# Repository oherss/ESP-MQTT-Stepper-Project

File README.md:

# ESP MQTT Stepper Project

This project is an integration between the TMC 2209 stepper driver with an ESP 32-S3 chip and code that allows the motor to connect via MQTT with a custom protocol.
The code parts of this project are made to be compatible with the PD Stepper hardware project.
The hardware is also inspired by this project, but without some of the extra bells and whistles, like PD power, expansion ports and buttons.

# This is a student project
Which means I am doing this for an exam and may not maintain this repo in the future, this is mostly a proof-of-concept.
This also means the directories may be kind of confusing, and there is also some extra code in here for an unrelated project, so don't mind my mess :)

# Hardware
The hardware, just like the PD-Stepper project is meant to be attached to the back of an ordinary Nema 17 stepper motor.
# PCB
As mentioned, this is based on the PD-Stepper project, but with just the essentials, mostly to make it cheaper to produce.
This means we still get the TMC 2209 silent stepper motor driver, and the flexible ESP-32-s3 microprocessor, but I have done away with the I2C and AUX port, USB-C Power Delivery and I have also replaced the unobtainum power-regulator (MPM-3612-33) and replaced it with a commonplace alternative.
In the PCB folder I have both the fabrication files, complete with BOM and assemply files, so you don't need to solder the components yourself.
The files have been prepared for them to be produced via JLC-PCB, so if you want to use another fabricator, the files may not work.
There is also the project files for KiCAD 7.0 files to work on the schematic if you'd like, although I have a few components with custom libraries, which might make it annoying to initially set up.
# Other Hardware
In the future I'd like to get some 3D-models for 3D-printing,so one could incase the driver on the back of the stepper motor. And more importantly, I'd like a insulation plate between the PCB and back of the motor, to avoid short-circuits.
I'd also like to make plans for a cable to connect the motor to the PCB, like there is included with the PD-Stepper.

# Software
I have 2 versions of the code for the stepper motor driver, but they are in very different states of development, the basic version was the first draft, to test the capabilities.
The advanced uses the serial communication with the driver, but also has many updates on the protocol, so I would generally reccomend that version.

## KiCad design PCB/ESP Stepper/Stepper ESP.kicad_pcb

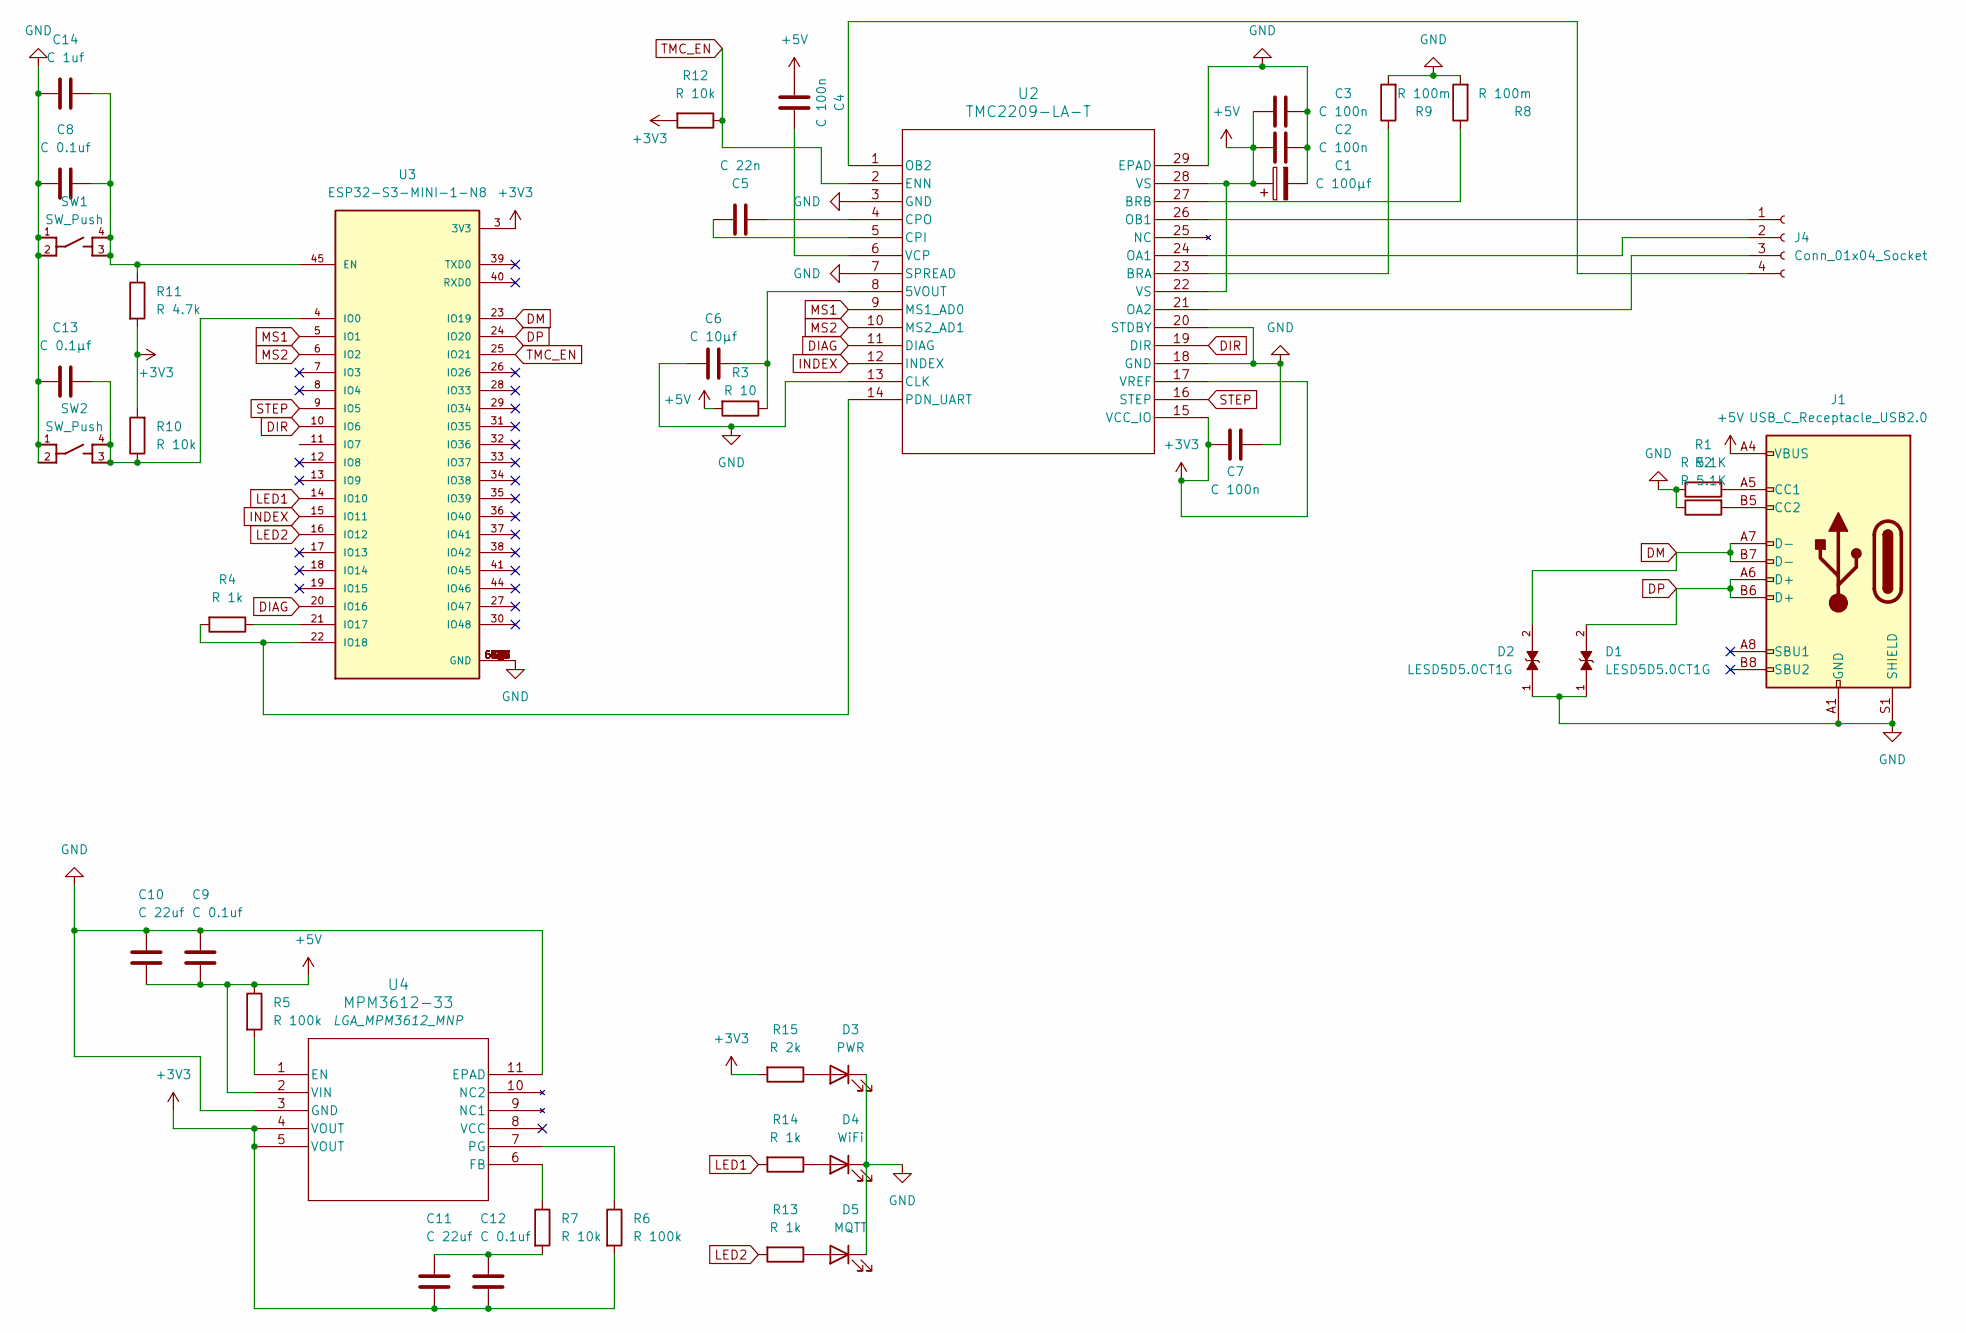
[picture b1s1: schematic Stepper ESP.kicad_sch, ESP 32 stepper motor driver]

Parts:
C1: C 100μf; CP_Elec_6.3x7.7
C2, C3, C4, C7: C 100n; Capacitor 0805
C5: C 22n; Capacitor 0402
C6: C 10μf; C 0603
C8, C9, C12: C 0.1uf; Capacitor 0805
C10, C11: C 22uf; Capacitor 0402
C13: C 0.1μf; Capacitor 0805
C14: C 1uf; Capacitor 0805
D1, D2: LESD5D5.0CT1G; TVS_LESD5D5.0CT1G; PARTREV O
D3: PWR; LED_0603_1608Metric
D4: WiFi; LED_0603_1608Metric
D5: MQTT; LED_0603_1608Metric
J1: USB_C_Receptacle_USB2.0; USB_C_Receptacle_G-Switch_GT-USB-7010ASV
J4: Conn_01x04_Socket; JST_EH_B4B-EH-A_1x04_P2.50mm_Vertical
R1, R2: R 5.1K; R_0603_1608Metric
R3: R 10; R_2512_6332Metric
R4, R13, R14: R 1k; R_0603_1608Metric
R5, R6: R 100k; R_0603_1608Metric
R7, R10, R12: R 10k; R_0603_1608Metric
R8, R9: R 100m; R_1206_3216Metric
R11: R 4.7k; R_0603_1608Metric
R15: R 2k; R_0603_1608Metric
SW1, SW2: SW_Push; SW_PTS810_SJM_250_SMTR_LFS
U2: TMC2209-LA-T; QFN28_5X5_3X8_EPAD_TRI
U3: ESP32-S3-MINI-1-N8; XCVR_ESP32-S3-MINI-1-N8; PARTREV v0.6
U4: MPM3612-33; LGA_MPM3612_MNP

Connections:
+3V3: C7.2, C11.2, C12.2, R6.2, R10.2, R11.2, R12.2, R15.2, U2.15 (VCC_IO), U2.17 (VREF), U3.3 (3V3), U4.4 (VOUT), U4.5 (VOUT)
+5V: C1.1, C2.2, C3.2, C4.2, C9.2, C10.2, J1.A4 (VBUS), J1.A9 (VBUS), J1.B4 (VBUS), J1.B9 (VBUS), R3.2, R5.1, U2.22 (VS), U2.28 (VS), U4.2 (VIN)
DIAG: U2.11 (DIAG), U3.20 (IO16)
DIR: U2.19 (DIR), U3.10 (IO6)
DM: D2.2, J1.A7 (D-), J1.B7 (D-), U3.23 (IO19)
DP: D1.2, J1.A6 (D+), J1.B6 (D+), U3.24 (IO20)
GND: C1.2, C2.1, C3.1, C6.2, C7.1, C8.2, C9.1, C10.1, C13.2, C14.2, D1.1, D2.1, D3.1 (K), D4.1 (K), D5.1 (K), J1.A1 (GND), J1.A12 (GND), J1.B1 (GND), J1.B12 (GND), J1.S1 (SHIELD), R1.1, R2.1, R8.2, R9.2, SW1.1, SW1.2, SW2.1, SW2.2, U2.3 (GND), U2.7 (SPREAD), U2.13 (CLK), U2.18 (GND), U2.20 (STDBY), U2.29 (EPAD), U3.1 (GND), U3.2 (GND), U3.42 (GND), U3.43 (GND), U3.46 (GND), U3.47 (GND), U3.48 (GND), U3.49 (GND), U3.50 (GND), U3.51 (GND), U3.52 (GND), U3.53 (GND), U3.54 (GND), U3.55 (GND), U3.56 (GND), U3.57 (GND), U3.58 (GND), U3.59 (GND), U3.60 (GND), U3.61 (GND), U3.61_1 (GND), U3.61_2 (GND), U3.61_3 (GND), U3.61_4 (GND), U3.61_5 (GND), U3.61_6 (GND), U3.61_7 (GND), U3.61_8 (GND), U3.62 (GND), U3.63 (GND), U3.64 (GND), U3.65 (GND), U4.3 (GND), U4.11 (EPAD)
INDEX: U2.12 (INDEX), U3.15 (IO11)
LED1: R14.2, U3.14 (IO10)
LED2: R13.2, U3.16 (IO12)
MS1: U2.9 (MS1_AD0), U3.5 (IO1)
MS2: U2.10 (MS2_AD1), U3.6 (IO2)
unnamed: C11.1, C12.1, R7.2
unnamed: D3.2 (A), R15.1
unnamed: D4.2 (A), R14.1
unnamed: D5.2 (A), R13.1
unnamed: J1.A5 (CC1), R1.2
unnamed: J1.B5 (CC2), R2.2
unnamed: J4.1, U2.26 (OB1)
unnamed: J4.2, U2.24 (OA1)
unnamed: J4.3, U2.21 (OA2)
unnamed: J4.4, U2.1 (OB2)
unnamed: C6.1, R3.1, U2.8 (5VOUT)
unnamed: R9.1, U2.23 (BRA)
unnamed: R8.1, U2.27 (BRB)
unnamed: C5.1, U2.5 (CPI)
unnamed: C5.2, U2.4 (CPO)
unnamed: R4.2, U2.14 (PDN_UART), U3.22 (IO18)
unnamed: C4.1, U2.6 (VCP)
unnamed: C8.1, C14.1, R11.1, SW1.3, SW1.4, U3.45 (EN)
unnamed: C13.1, R10.1, SW2.3, SW2.4, U3.4 (IO0)
unnamed: R4.1, U3.21 (IO17)
unnamed: R5.2, U4.1 (EN)
unnamed: R7.1, U4.6 (FB)
unnamed: R6.1, U4.7 (PG)
STEP: U2.16 (STEP), U3.9 (IO5)
TMC_EN: R12.1, U2.2 (ENN), U3.25 (IO21)

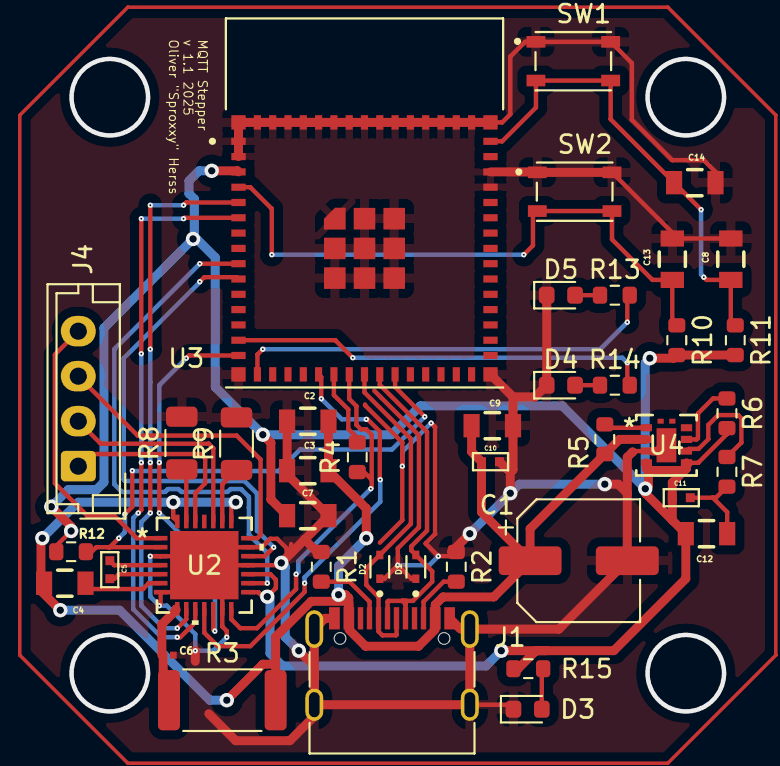
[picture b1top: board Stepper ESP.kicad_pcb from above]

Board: 2 copper layers, 41 parts (0 on the bottom side), 37 nets.

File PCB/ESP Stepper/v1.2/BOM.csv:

Id;Designator;Footprint;Quantity;Comment;Supplier and ref
1;U2;QFN28_5X5_3X8_EPAD_TRI;1;TMC2209-LA-T;
2;U1;SOT-223-3_TabPin2;1;AMS1117-3.3;
3;C7,C4,C3,C2;Capacitor 0805;4;C 100n;
4;R12,R10;R_0603_1608Metric;2;R 10k;
5;R9,R8;R_1206_3216Metric;2;R 100m;
6;C6;C 0603;1;C 10μf;
7;C14;Capacitor 0805;1;C 1uf;
8;J4;JST_EH_B4B-EH-A_1x04_P2.50mm_Vertical;1;Conn_01x04_Socket;
9;R11;R_0603_1608Metric;1;R 4.7k;
10;C13;Capacitor 0805;1;C 0.1μf;
11;R2,R1;R_0603_1608Metric;2;R 5.1K;
12;D5;LED_0603_1608Metric;1;MQTT;
13;U3;XCVR_ESP32-S3-MINI-1-N8;1;ESP32-S3-MINI-1-N8;
14;SW2,SW1;SW_PTS810_SJM_250_SMTR_LFS;2;SW_Push;
15;R3;R_2512_6332Metric;1;R 10;
16;R15;R_0603_1608Metric;1;R 2k;
17;D3;LED_0603_1608Metric;1;PWR;
18;D4;LED_0603_1608Metric;1;WiFi;
19;R14,R13,R4;R_0603_1608Metric;3;R 1k;
20;J1;USB_C_Receptacle_G-Switch_GT-USB-7010ASV;1;USB_C_Receptacle_USB2.0;
21;D2,D1;TVS_LESD5D5.0CT1G;2;LESD5D5.0CT1G;
22;C1;CP_Elec_6.3x7.7;1;C 100μf;
23;C8;Capacitor 0805;1;C 0.1uf;
24;C5;Capacitor 0402;1;C 22n;

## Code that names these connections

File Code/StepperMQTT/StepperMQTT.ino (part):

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/////////////////////////

//TMC2209 Stepper Driver
#define TMC_EN  21 //Low to enable motor, high to disable)
#define STEP    5
#define DIR     6
#define MS1     1
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#define SPREAD  7
#define TMC_TX  17
#define TMC_RX  18
#define DIAG    16
#define INDEX   11

//PD Trigger (CH224K)
#define PG      15  //power good singnal (dont enable stepper untill this is good)
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//Other
#define VBUS    4
#define NTC     7
#define LED1    10
#define LED2    12

/////////////////////////////
// Global Variable Defines //
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}

void setup() {
  pinMode(LED1, OUTPUT);
  pinMode(LED2, OUTPUT);
  
    //PD Trigger Setup
  pinMode(PG, INPUT);
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  digitalWrite(CFG3, LOW);  //  -    0     1     1     0
  
  //Stepper simple setup (no serial comms)
  pinMode(TMC_EN, OUTPUT);
  pinMode(STEP, OUTPUT);
  pinMode(DIR, OUTPUT);
  pinMode(MS1, OUTPUT);
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
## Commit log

2025-05-05 More refined code as well as more comments
